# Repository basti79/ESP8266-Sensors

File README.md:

# ESP8266-Sensors

IoT sensor modules based on ESP8266 for my home automation project.

This little module can connect the following devices:
* DS18B20 1-wire temperature sensors
* DHT-22 combined temperature and humidity sensor
* HR20 controller with [OpenHR20 Firmware](https://sourceforge.net/projects/openhr20/)

It's based on the Arduino [Arduino core for ESP8266](https://github.com/esp8266/Arduino) and needs these libraries:
* [WiFiManager](https://github.com/tzapu/WiFiManager)
* [Arduino Client for MQTT](https://github.com/knolleary/pubsubclient)
* [Teensy OneWire Library](http://www.pjrc.com/teensy/td_libs_OneWire.html)
* [Arduino Library for Maxim Temperature Integrated Circuits](https://github.com/milesburton/Arduino-Temperature-Control-Library)

For more information and schematics please visit: https://www.basti79.de/mediawiki/index.php/1-Wire_Sensoren_mit_WLAN

**This is the master branch:**
* uses an ESP-12 Module
* will get an aditional interface for reading information from water meters soon

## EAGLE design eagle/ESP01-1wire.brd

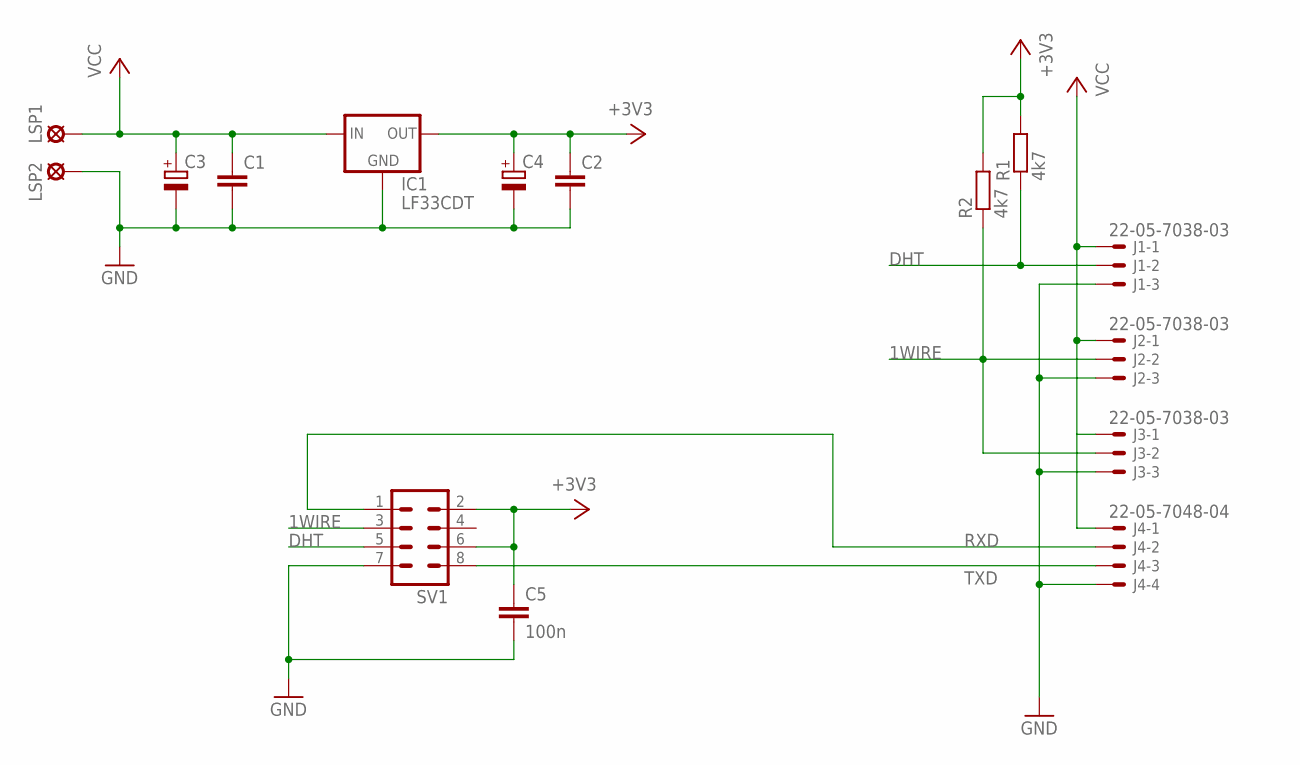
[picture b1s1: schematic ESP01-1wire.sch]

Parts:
C1, C2: C-EUC0805; C0805
C3, C4: CPOL-EUSMCA; SMC_A
C5: 100n; C0805
IC1: LF33CDT; DPACK
J1, J2, J3: 22-05-7038-03; 7395-03
J4: 22-05-7048-04; 7395-04
LSP1, LSP2: LSP10
R1, R2: 4k7; R0805
SV1: MA04-2

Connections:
1WIRE: J2.2, J3.2, R2.1, SV1.3
+3V3: C2.1, C4.+, C5.1, IC1.3 (OUT), R1.2, R2.2, SV1.2, SV1.6
DHT: J1.2, R1.1, SV1.5
GND: C1.2, C2.2, C3.-, C4.-, C5.2, IC1.4 (GND), J1.3, J2.3, J3.3, J4.4, LSP2.MP, SV1.7
RXD: J4.2, SV1.1
TXD: J4.3, SV1.8
VCC: C1.1, C3.+, IC1.1 (IN), J1.1, J2.1, J3.1, J4.1, LSP1.MP

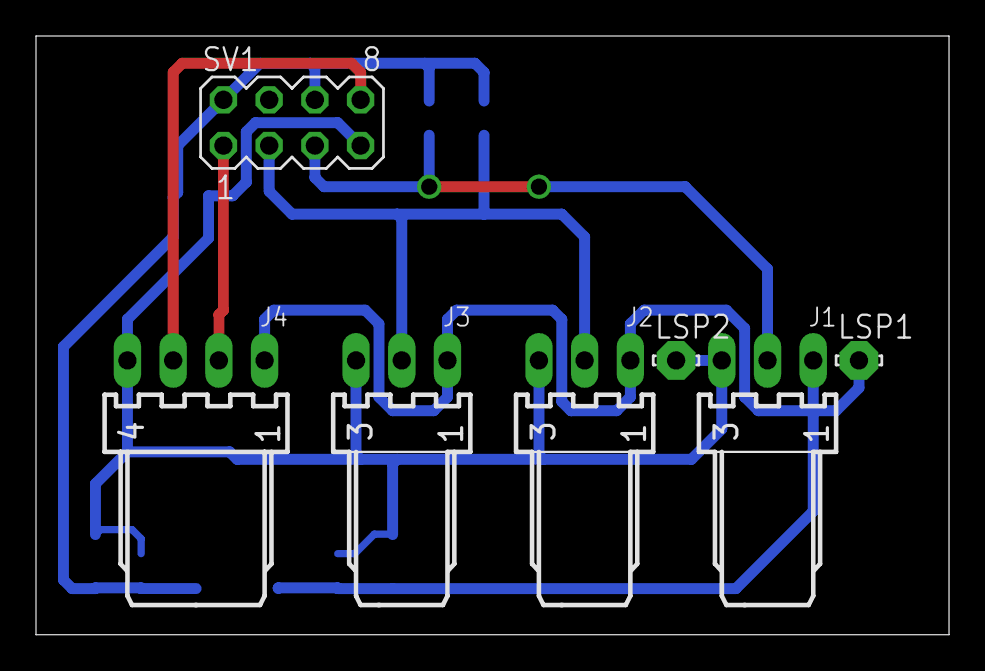
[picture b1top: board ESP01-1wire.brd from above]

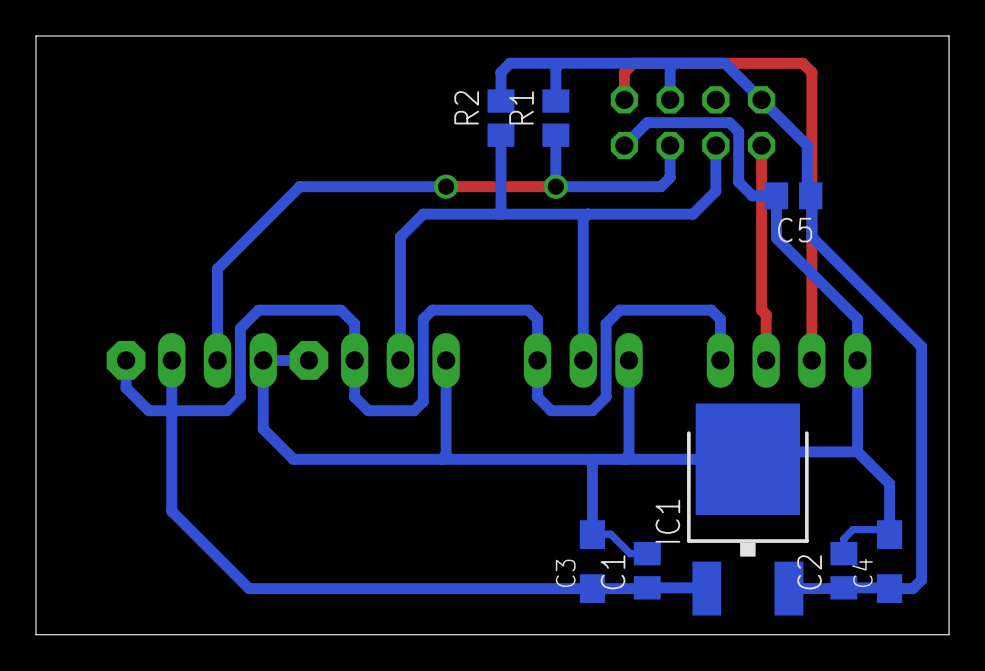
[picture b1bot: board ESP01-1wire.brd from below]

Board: 2 copper layers, 50.7 x 33.3 mm, 15 parts (8 on the bottom side), 7 nets.

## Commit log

2016-05-30 Initial version of code, schematic and documentation.
2016-05-30 new version with ESP-12 module
